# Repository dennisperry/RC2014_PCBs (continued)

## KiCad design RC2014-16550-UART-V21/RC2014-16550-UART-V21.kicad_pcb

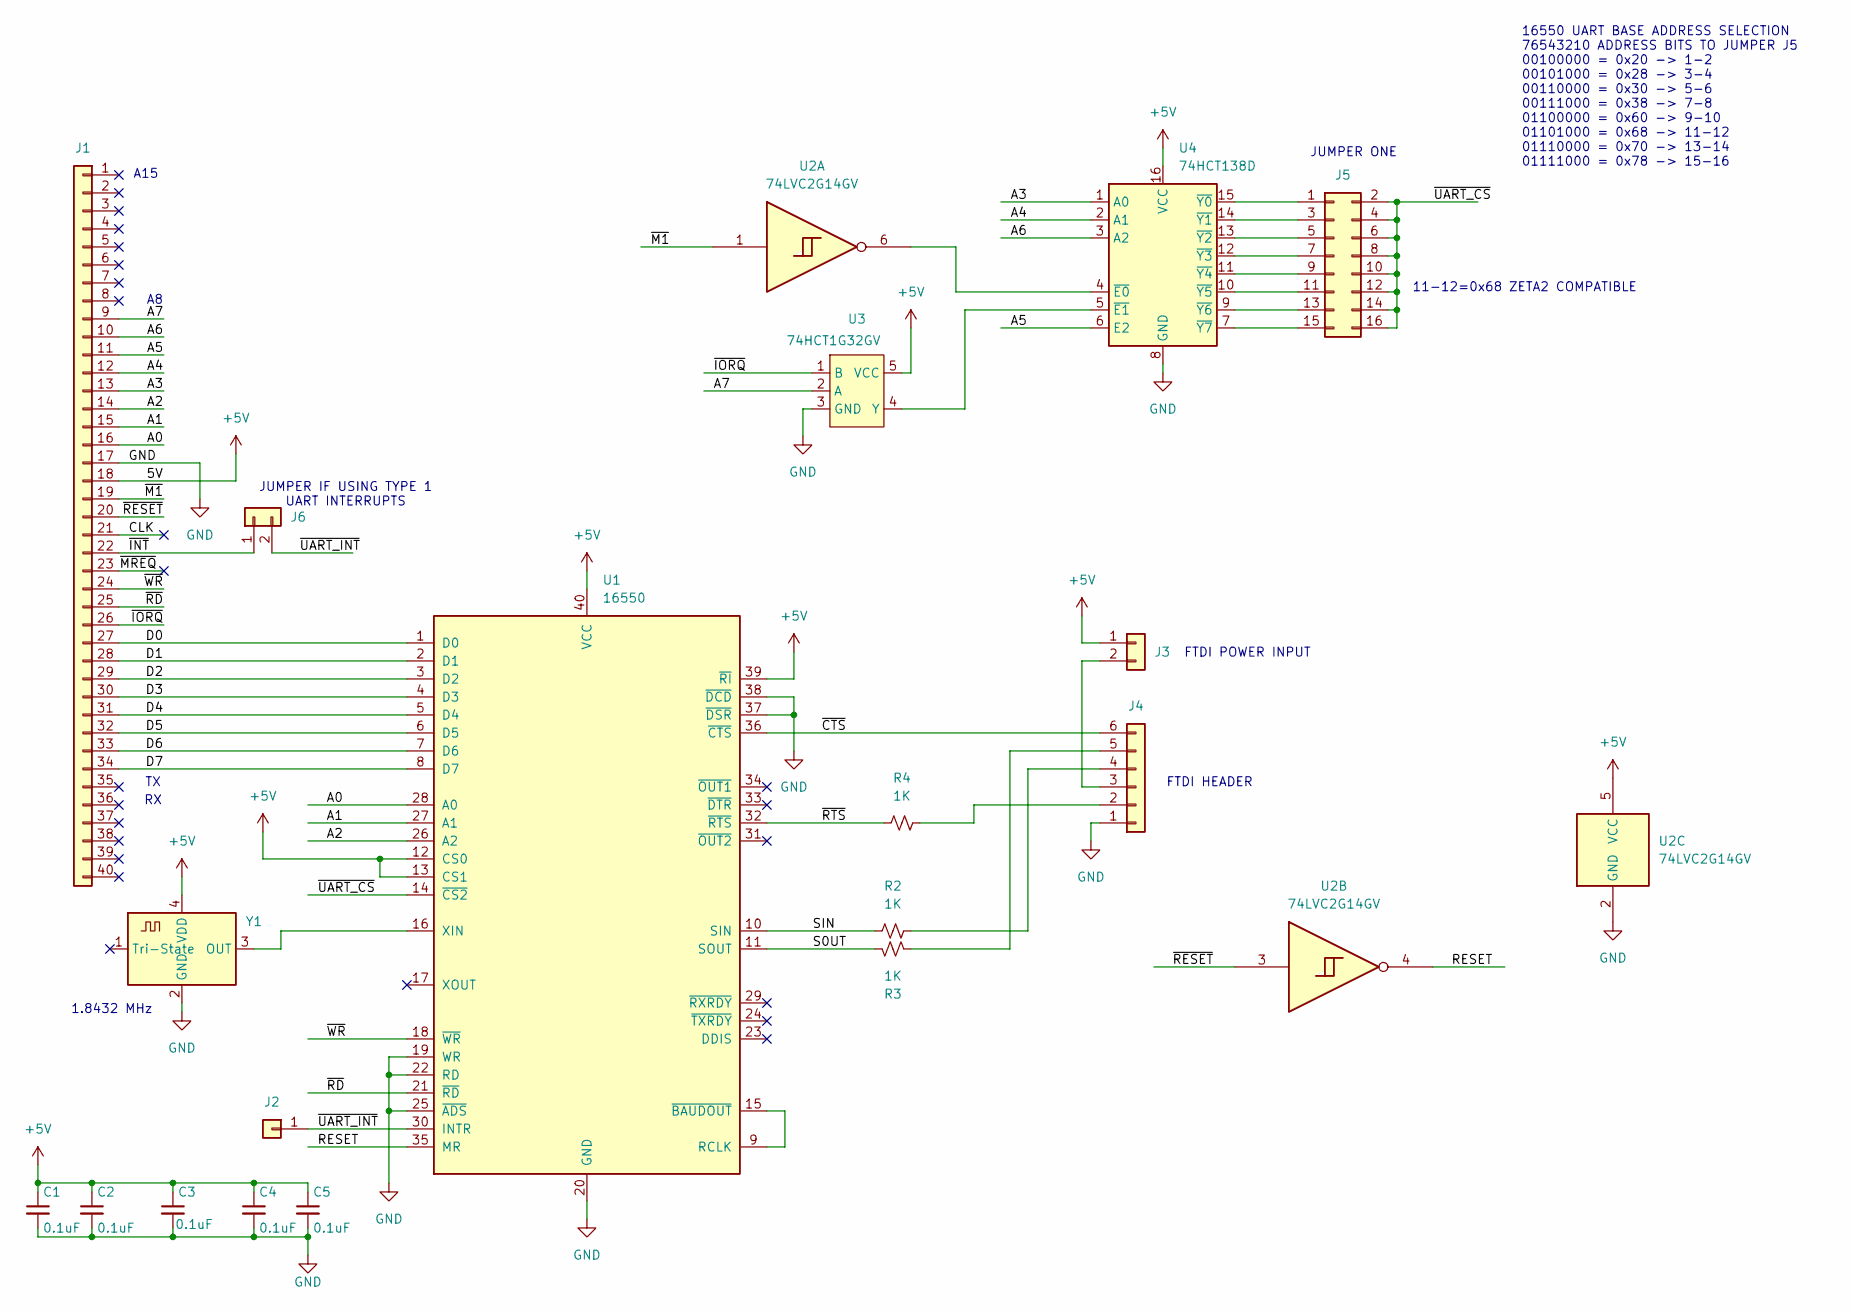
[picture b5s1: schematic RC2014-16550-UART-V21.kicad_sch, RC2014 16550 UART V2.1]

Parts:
C1, C2, C3, C4, C5: 0.1uF; C_0805_2012Metric_Pad1.18x1.45mm_HandSolder
J1: Conn_01x40; PinHeader_1x40_P2.54mm_Vertical
J2: Conn_01x01; PinHeader_1x01_P2.54mm_Vertical
J3, J6: Conn_01x02; PinHeader_1x02_P2.54mm_Vertical
J4: Conn_01x06; PinHeader_1x06_P2.54mm_Vertical
J5: Conn_02x08_Odd_Even; PinHeader_2x08_P2.54mm_Vertical
R2, R3, R4: 1K; R_0805_2012Metric_Pad1.20x1.40mm_HandSolder
U1: 16550; DIP-40_W15.24mm
U2: 74LVC2G14GV; SC-74-6_1.55x2.9mm_P0.95mm
U3: 74HCT1G32GV; SOT-23-5_HandSoldering
U4: 74HCT138D; SOIC-16_4.55x10.3mm_P1.27mm
Y1: ASCO; Oscillator_SMD_EuroQuartz_XO91-4Pin_7.0x5.0mm_HandSoldering

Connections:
+5V: C1.1, C2.1, C3.1, C4.1, C5.1, J1.18, J3.1, U1.12 (CS0), U1.13 (CS1), U1.39 (~RI), U1.40 (VCC), U2.5 (VCC), U3.5 (VCC), U4.16 (VCC), Y1.4 (VDD)
/A0: J1.16, U1.28 (A0)
/A1: J1.15, U1.27 (A1)
/A2: J1.14, U1.26 (A2)
/A3: J1.13, U4.1 (A0)
/A4: J1.12, U4.2 (A1)
/A5: J1.11, U4.6 (E2)
/A6: J1.10, U4.3 (A2)
/A7: J1.9, U3.2 (A)
/CLK: J1.21
/D0: J1.27, U1.1 (D0)
/D1: J1.28, U1.2 (D1)
/D2: J1.29, U1.3 (D2)
/D3: J1.30, U1.4 (D3)
/D4: J1.31, U1.5 (D4)
/D5: J1.32, U1.6 (D5)
/D6: J1.33, U1.7 (D6)
/D7: J1.34, U1.8 (D7)
/RESET: U1.35 (MR), U2.4
/S0UT: R3.2, U1.11 (SOUT)
/SIN: R2.1, U1.10 (SIN)
/~CTS: J4.6, U1.36 (~CTS)
/~INT: J1.22, J6.1
/~IORQ: J1.26, U3.1 (B)
/~M1: J1.19, U2.1
/~MREQ: J1.23
/~RD: J1.25, U1.21 (~RD)
/~RESET: J1.20, U2.3
/~RTS: R4.1, U1.32 (~RTS)
/~UART_CS: J5.2, J5.4, J5.6, J5.8, J5.10, J5.12, J5.14, J5.16, U1.14 (~CS2)
/~UART_INT: J2.1, J6.2, U1.30 (INTR)
/~WR: J1.24, U1.18 (~WR)
GND: C1.2, C2.2, C3.2, C4.2, C5.2, J1.17, J4.1, U1.19 (WR), U1.20 (GND), U1.22 (RD), U1.25 (~ADS), U1.37 (~DSR), U1.38 (~DCD), U2.2 (GND), U3.3 (GND), U4.8 (GND), Y1.2 (GND)
unnamed: J3.2, J4.3
unnamed: J4.2, R4.2
unnamed: J4.4, R2.2
unnamed: J4.5, R3.1
unnamed: J5.1, U4.15 (~Y0)
unnamed: J5.3, U4.14 (~Y1)
unnamed: J5.5, U4.13 (~Y2)
unnamed: J5.7, U4.12 (~Y3)
unnamed: J5.9, U4.11 (~Y4)
unnamed: J5.11, U4.10 (~Y5)
unnamed: J5.13, U4.9 (~Y6)
unnamed: J5.15, U4.7 (~Y7)
unnamed: U1.9 (RCLK), U1.15 (~BAUDOUT)
unnamed: U1.16 (XIN), Y1.3 (OUT)
unnamed: U3.4 (Y), U4.5 (~E1)
unnamed: U2.6, U4.4 (~E0)

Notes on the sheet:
16550 UART BASE ADDRESS SELECTION 76543210 ADDRESS BITS TO JUMPER J5 00100000 = 0x20 -> 1-2 00101000 = 0x28 -> 3-4 00110000 = 0x30 -> 5-6 00111000 = 0x38 -> 7-8 01100000 = 0x60 -> 9-10 01101000 = 0x68 -> 11-12 01110000 = 0x70 -> 13-14 01111000 = 0x78 -> 15-16
11-12=0x68 ZETA2 COMPATIBLE
JUMPER ONE
1.8432 MHz
JUMPER IF USING TYPE 1 UART INTERRUPTS
FTDI POWER INPUT
A15
FTDI HEADER

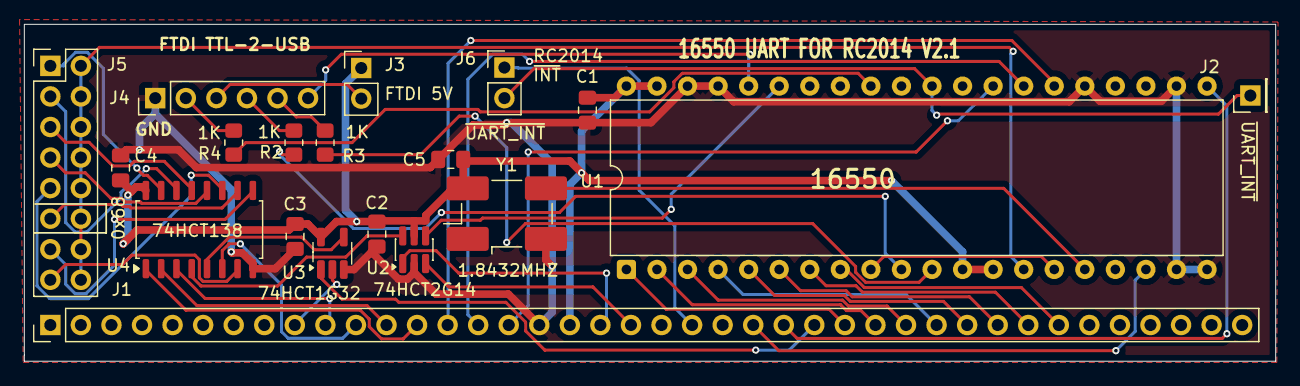
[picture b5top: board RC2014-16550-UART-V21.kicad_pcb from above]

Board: 2 copper layers, 104.0 x 28.0 mm, 19 parts (0 on the bottom side), 47 nets.

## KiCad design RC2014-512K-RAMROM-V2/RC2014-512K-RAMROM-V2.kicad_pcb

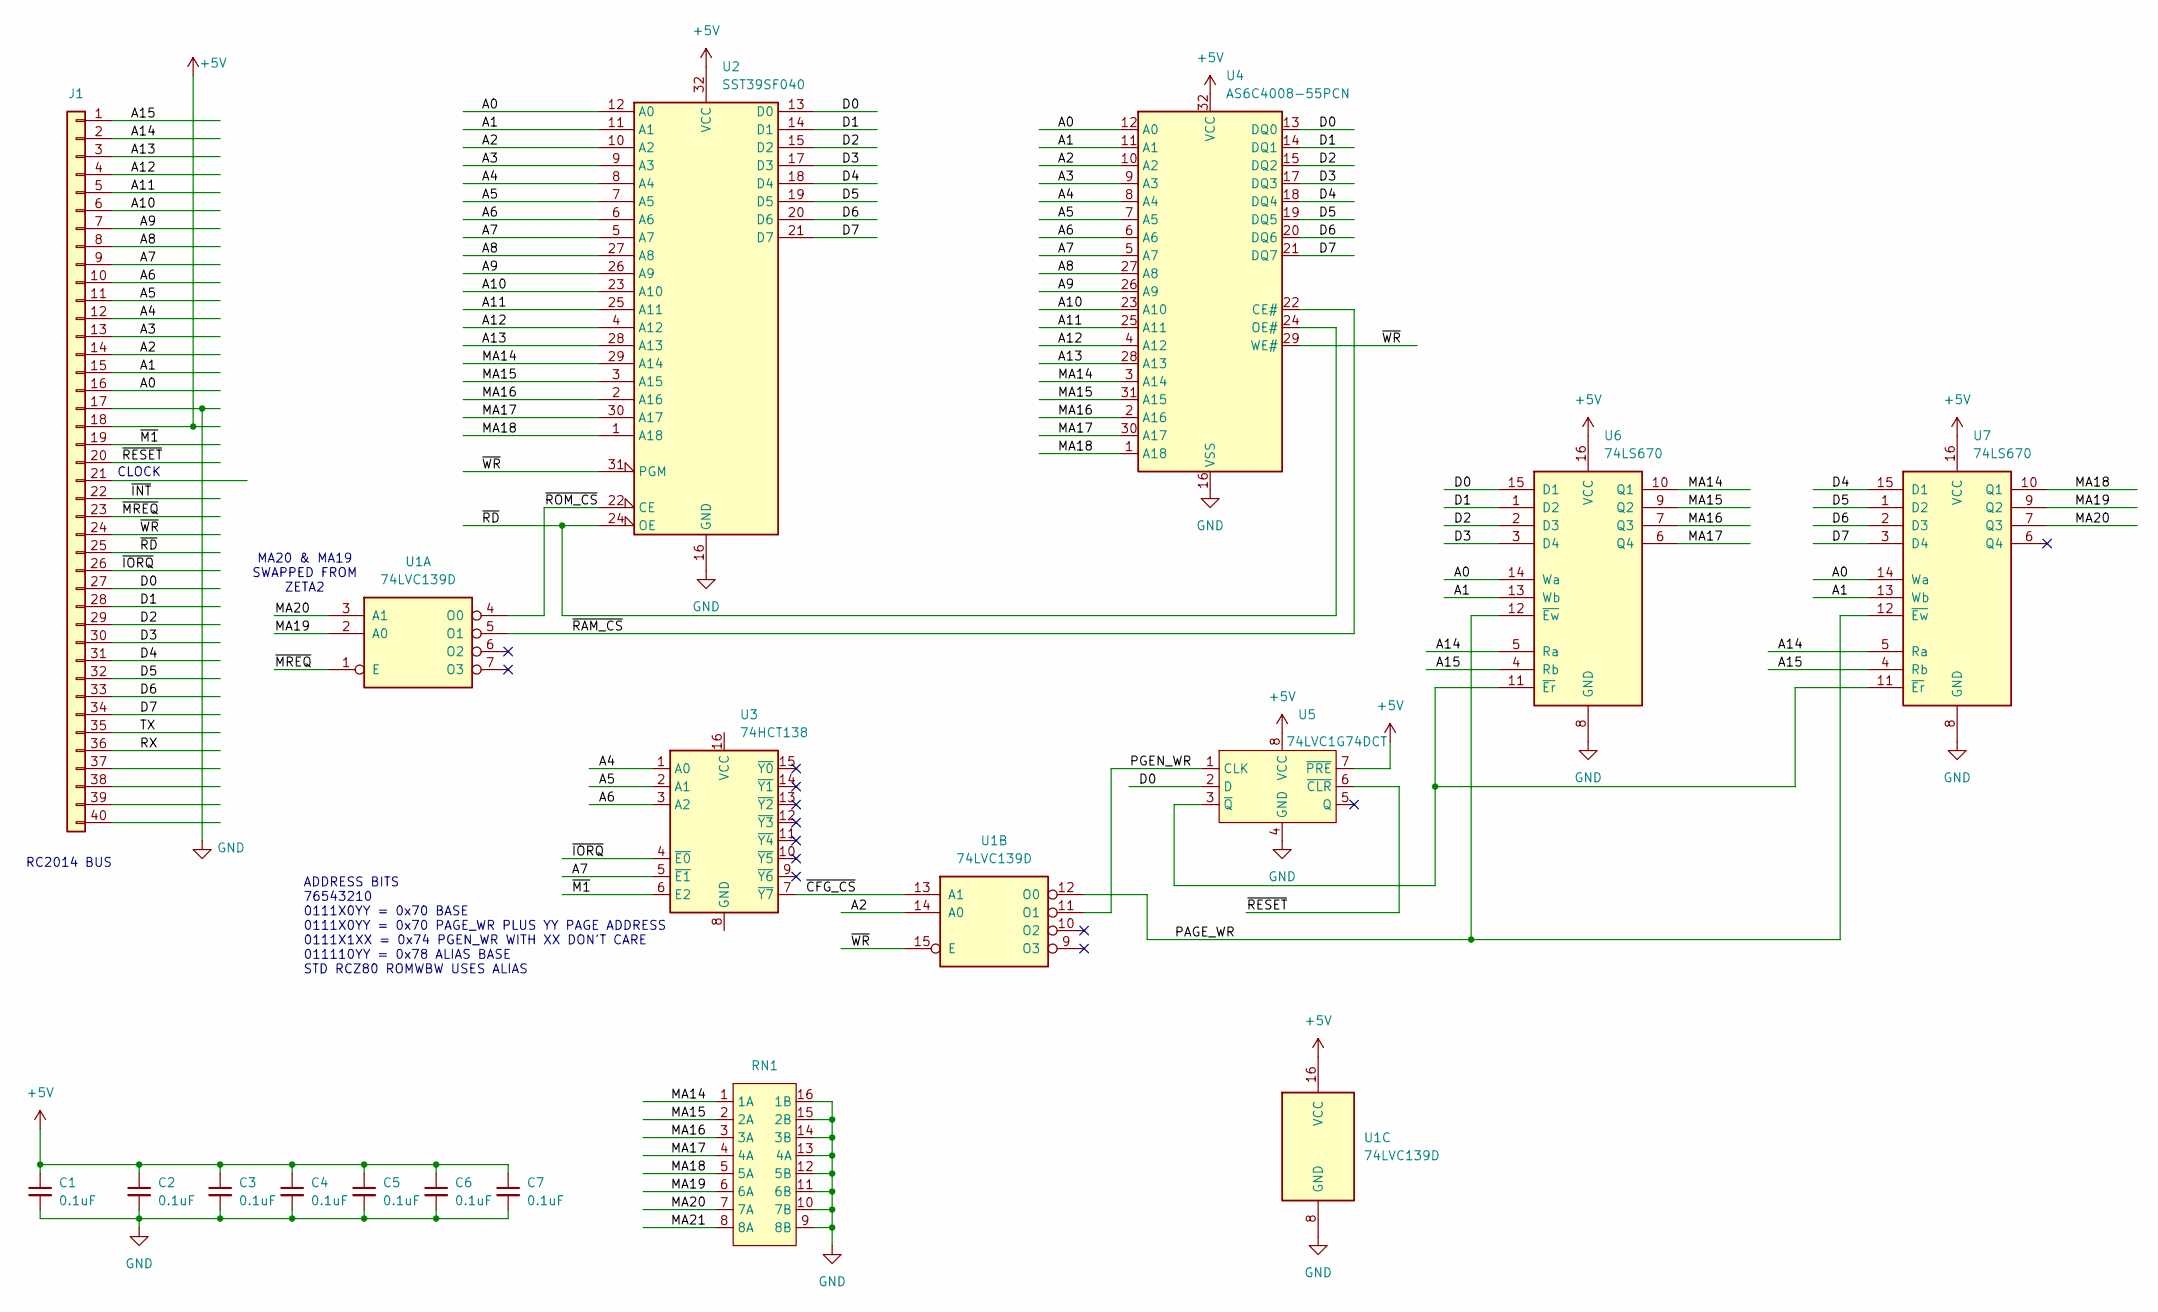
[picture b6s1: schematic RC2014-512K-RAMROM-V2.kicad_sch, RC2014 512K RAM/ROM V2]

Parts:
C1, C2, C3, C4, C5, C6, C7: 0.1uF; C_0805_2012Metric_Pad1.18x1.45mm_HandSolder
J1: Conn_01x40; PinHeader_1x40_P2.54mm_Vertical
RN1: SOIC-16W_5.3x10.2mm_P1.27mm
U1: 74LVC139D; SOIC-16_4.55x10.3mm_P1.27mm
U2: SST39SF040; DIP_Socket-32_DP_W11.9mm_W12.7mm_W15.24mm_W17.78mm_W18.5mm_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
U3: 74HCT138; SOIC-16_4.55x10.3mm_P1.27mm
U4: AS6C4008-55PCN; SOP-32_11.305x20.495mm_P1.27mm
U5: 74LVC1G74DCT; SSOP-8_2.95x2.8mm_P0.65mm
U6, U7: 74LS670; SOIC-16_4.55x10.3mm_P1.27mm

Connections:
+5V: C1.1, C2.1, C3.1, C4.1, C5.1, C6.1, C7.1, J1.18, U1.16 (VCC), U2.32 (VCC), U4.32 (VCC), U5.7 (~PRE), U5.8 (VCC), U6.16 (VCC), U7.16 (VCC)
/A0: J1.16, U2.12 (A0), U4.12 (A0), U6.14 (Wa), U7.14 (Wa)
/A1: J1.15, U2.11 (A1), U4.11 (A1), U6.13 (Wb), U7.13 (Wb)
/A2: J1.14, U1.14 (A0), U2.10 (A2), U4.10 (A2)
/A3: J1.13, U2.9 (A3), U4.9 (A3)
/A4: J1.12, U2.8 (A4), U3.1 (A0), U4.8 (A4)
/A5: J1.11, U2.7 (A5), U3.2 (A1), U4.7 (A5)
/A6: J1.10, U2.6 (A6), U3.3 (A2), U4.6 (A6)
/A7: J1.9, U2.5 (A7), U3.5 (~E1), U4.5 (A7)
/A8: J1.8, U2.27 (A8), U4.27 (A8)
/A9: J1.7, U2.26 (A9), U4.26 (A9)
/A10: J1.6, U2.23 (A10), U4.23 (A10)
/A11: J1.5, U2.25 (A11), U4.25 (A11)
/A12: J1.4, U2.4 (A12), U4.4 (A12)
/A13: J1.3, U2.28 (A13), U4.28 (A13)
/A14: J1.2, U6.5 (Ra), U7.5 (Ra)
/A15: J1.1, U6.4 (Rb), U7.4 (Rb)
/D0: J1.27, U2.13 (D0), U4.13 (DQ0), U5.2 (D), U6.15 (D1)
/D1: J1.28, U2.14 (D1), U4.14 (DQ1), U6.1 (D2)
/D2: J1.29, U2.15 (D2), U4.15 (DQ2), U6.2 (D3)
/D3: J1.30, U2.17 (D3), U4.17 (DQ3), U6.3 (D4)
/D4: J1.31, U2.18 (D4), U4.18 (DQ4), U7.15 (D1)
/D5: J1.32, U2.19 (D5), U4.19 (DQ5), U7.1 (D2)
/D6: J1.33, U2.20 (D6), U4.20 (DQ6), U7.2 (D3)
/D7: J1.34, U2.21 (D7), U4.21 (DQ7), U7.3 (D4)
/MA14: RN1.1 (1A), U2.29 (A14), U4.3 (A14), U6.10 (Q1)
/MA15: RN1.2 (2A), U2.3 (A15), U4.31 (A15), U6.9 (Q2)
/MA16: RN1.3 (3A), U2.2 (A16), U4.2 (A16), U6.7 (Q3)
/MA17: RN1.4 (4A), U2.30 (A17), U4.30 (A17), U6.6 (Q4)
/MA18: RN1.5 (5A), U2.1 (A18), U4.1 (A18), U7.10 (Q1)
/MA19: RN1.6 (6A), U1.2 (A0), U7.9 (Q2)
/MA20: RN1.7 (7A), U1.3 (A1), U7.7 (Q3)
/MA21: RN1.8 (8A)
/PAGE_WR: U1.12 (O0), U6.12 (~Ew), U7.12 (~Ew)
/PGEN_WR: U1.11 (O1), U5.1 (CLK)
/RX: J1.36
/TX: J1.35
/~CFG_CS: U1.13 (A1), U3.7 (~Y7)
/~INT: J1.22
/~IORQ: J1.26, U3.4 (~E0)
/~M1: J1.19, U3.6 (E2)
/~MREQ: J1.23, U1.1 (E)
/~RAM_CS: U1.5 (O1), U4.22 (CE#)
/~RD: J1.25, U2.24 (OE), U4.24 (OE#)
/~RESET: J1.20, U5.6 (~CLR)
/~ROM_CS: U1.4 (O0), U2.22 (CE)
/~WR: J1.24, U1.15 (E), U2.31 (PGM), U4.29 (WE#)
GND: C1.2, C2.2, C3.2, C4.2, C5.2, C6.2, C7.2, J1.17, RN1.9 (8B), RN1.10 (7B), RN1.11 (6B), RN1.12 (5B), RN1.13 (4A), RN1.14 (3B), RN1.15 (2B), RN1.16 (1B), U1.8 (GND), U2.16 (GND), U4.16 (VSS), U5.4 (GND), U6.8 (GND), U7.8 (GND)
unnamed: U5.3 (~Q), U6.11 (~Er), U7.11 (~Er)

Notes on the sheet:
ADDRESS BITS 76543210 0111X0YY = 0x70 BASE 0111X0YY = 0x70 PAGE_WR PLUS YY PAGE ADDRESS 0111X1XX = 0x74 PGEN_WR WITH XX DON'T CARE 011110YY = 0x78 ALIAS BASE STD RCZ80 ROMWBW USES ALIAS
RC2014 BUS
MA20 & MA19 SWAPPED FROM ZETA2
CLOCK

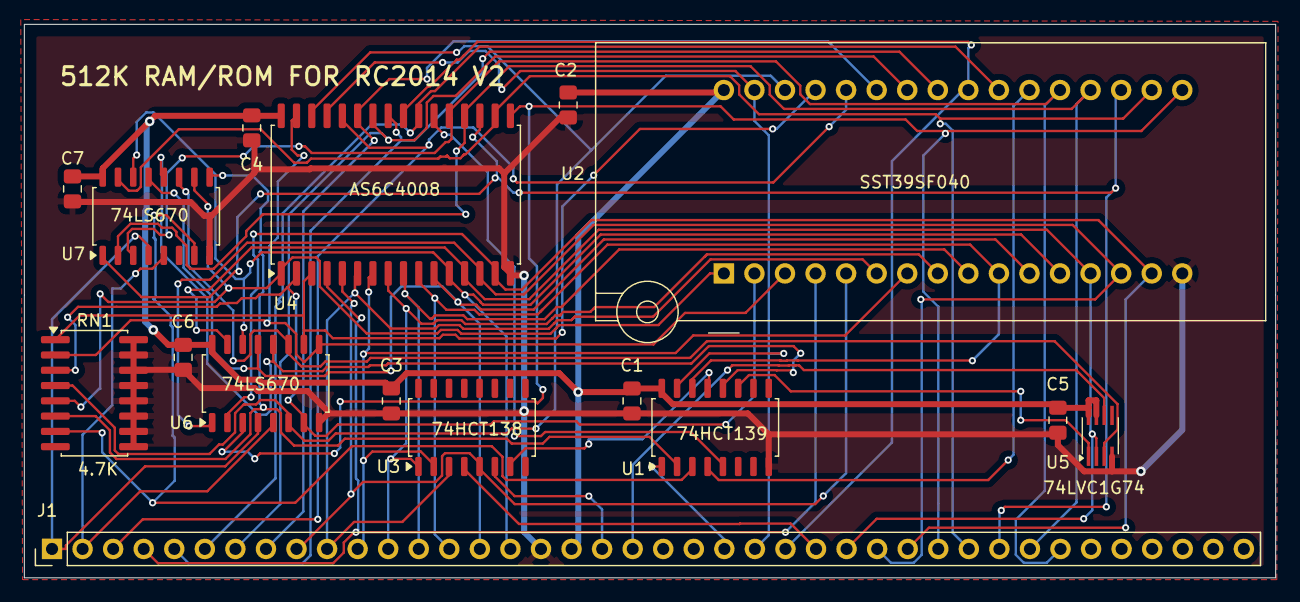
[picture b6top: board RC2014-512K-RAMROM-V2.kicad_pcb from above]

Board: 2 copper layers, 104.0 x 46.0 mm, 16 parts (0 on the bottom side), 45 nets.

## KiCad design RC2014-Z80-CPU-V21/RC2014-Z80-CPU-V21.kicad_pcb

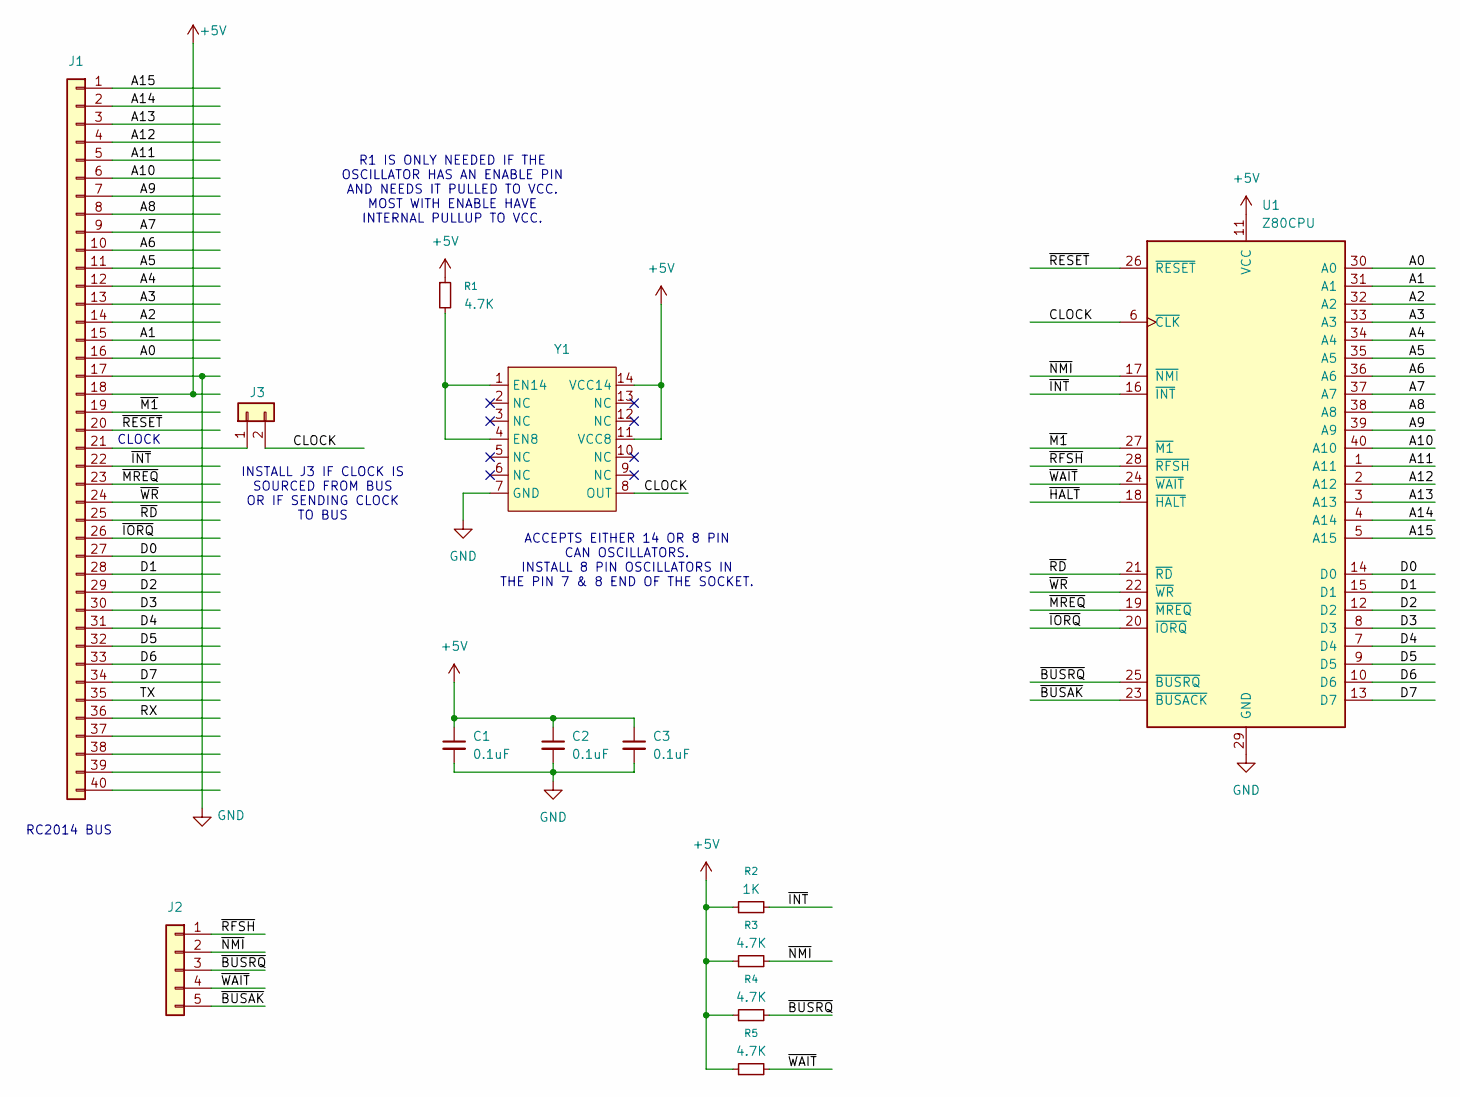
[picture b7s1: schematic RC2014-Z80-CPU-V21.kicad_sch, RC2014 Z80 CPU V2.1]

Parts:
C1, C2, C3: 0.1uF; C_0805_2012Metric_Pad1.18x1.45mm_HandSolder
J1: Conn_01x40; PinHeader_1x40_P2.54mm_Vertical
J2: Conn_01x05; PinHeader_1x05_P2.54mm_Vertical
J3: Conn_01x02; PinHeader_2x01_P2.54mm_Vertical
R1, R3, R4, R5: 4.7K; R_0805_2012Metric_Pad1.20x1.40mm_HandSolder
R2: 1K; R_0805_2012Metric_Pad1.20x1.40mm_HandSolder
U1: Z80CPU; DIP-40_W15.24mm
Y1: DIP-14_W7.62mm

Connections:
+5V: C1.1, C2.1, C3.1, J1.18, R1.1, R2.1, R3.1, R4.1, R5.1, U1.11 (VCC), Y1.11 (VCC8), Y1.14 (VCC14)
/A0: J1.16, U1.30 (A0)
/A1: J1.15, U1.31 (A1)
/A2: J1.14, U1.32 (A2)
/A3: J1.13, U1.33 (A3)
/A4: J1.12, U1.34 (A4)
/A5: J1.11, U1.35 (A5)
/A6: J1.10, U1.36 (A6)
/A7: J1.9, U1.37 (A7)
/A8: J1.8, U1.38 (A8)
/A9: J1.7, U1.39 (A9)
/A10: J1.6, U1.40 (A10)
/A11: J1.5, U1.1 (A11)
/A12: J1.4, U1.2 (A12)
/A13: J1.3, U1.3 (A13)
/A14: J1.2, U1.4 (A14)
/A15: J1.1, U1.5 (A15)
/CLOCK: J3.2, U1.6 (~CLK), Y1.8 (OUT)
/D0: J1.27, U1.14 (D0)
/D1: J1.28, U1.15 (D1)
/D2: J1.29, U1.12 (D2)
/D3: J1.30, U1.8 (D3)
/D4: J1.31, U1.7 (D4)
/D5: J1.32, U1.9 (D5)
/D6: J1.33, U1.10 (D6)
/D7: J1.34, U1.13 (D7)
/RX: J1.36
/TX: J1.35
/~BUSAK: J2.5, U1.23 (~BUSACK)
/~BUSRQ: J2.3, R4.2, U1.25 (~BUSRQ)
/~HALT: U1.18 (~HALT)
/~INT: J1.22, R2.2, U1.16 (~INT)
/~IORQ: J1.26, U1.20 (~IORQ)
/~M1: J1.19, U1.27 (~M1)
/~MREQ: J1.23, U1.19 (~MREQ)
/~NMI: J2.2, R3.2, U1.17 (~NMI)
/~RD: J1.25, U1.21 (~RD)
/~RESET: J1.20, U1.26 (~RESET)
/~RFSH: J2.1, U1.28 (~RFSH)
/~WAIT: J2.4, R5.2, U1.24 (~WAIT)
/~WR: J1.24, U1.22 (~WR)
GND: C1.2, C2.2, C3.2, J1.17, U1.29 (GND), Y1.7 (GND)
unnamed: J1.21, J3.1
unnamed: R1.2, Y1.1 (EN14), Y1.4 (EN8)

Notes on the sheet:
RC2014 BUS
INSTALL J3 IF CLOCK IS SOURCED FROM BUS OR IF SENDING CLOCK TO BUS
ACCEPTS EITHER 14 OR 8 PIN CAN OSCILLATORS. INSTALL 8 PIN OSCILLATORS IN THE PIN 7 & 8 END OF THE SOCKET.
CLOCK
R1 IS ONLY NEEDED IF THE OSCILLATOR HAS AN ENABLE PIN AND NEEDS IT PULLED TO VCC. MOST WITH ENABLE HAVE INTERNAL PULLUP TO VCC.

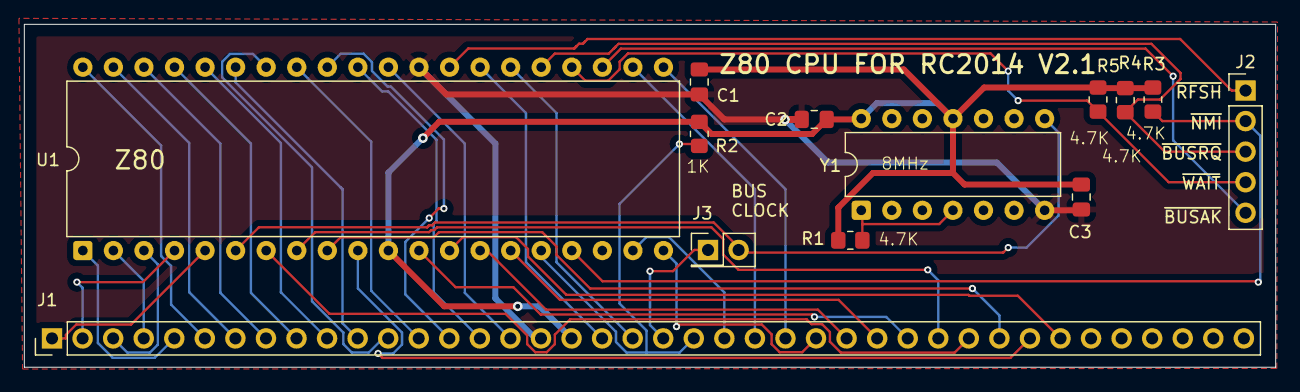
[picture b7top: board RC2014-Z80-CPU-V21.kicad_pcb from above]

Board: 2 copper layers, 104.0 x 28.5 mm, 13 parts (0 on the bottom side), 41 nets.

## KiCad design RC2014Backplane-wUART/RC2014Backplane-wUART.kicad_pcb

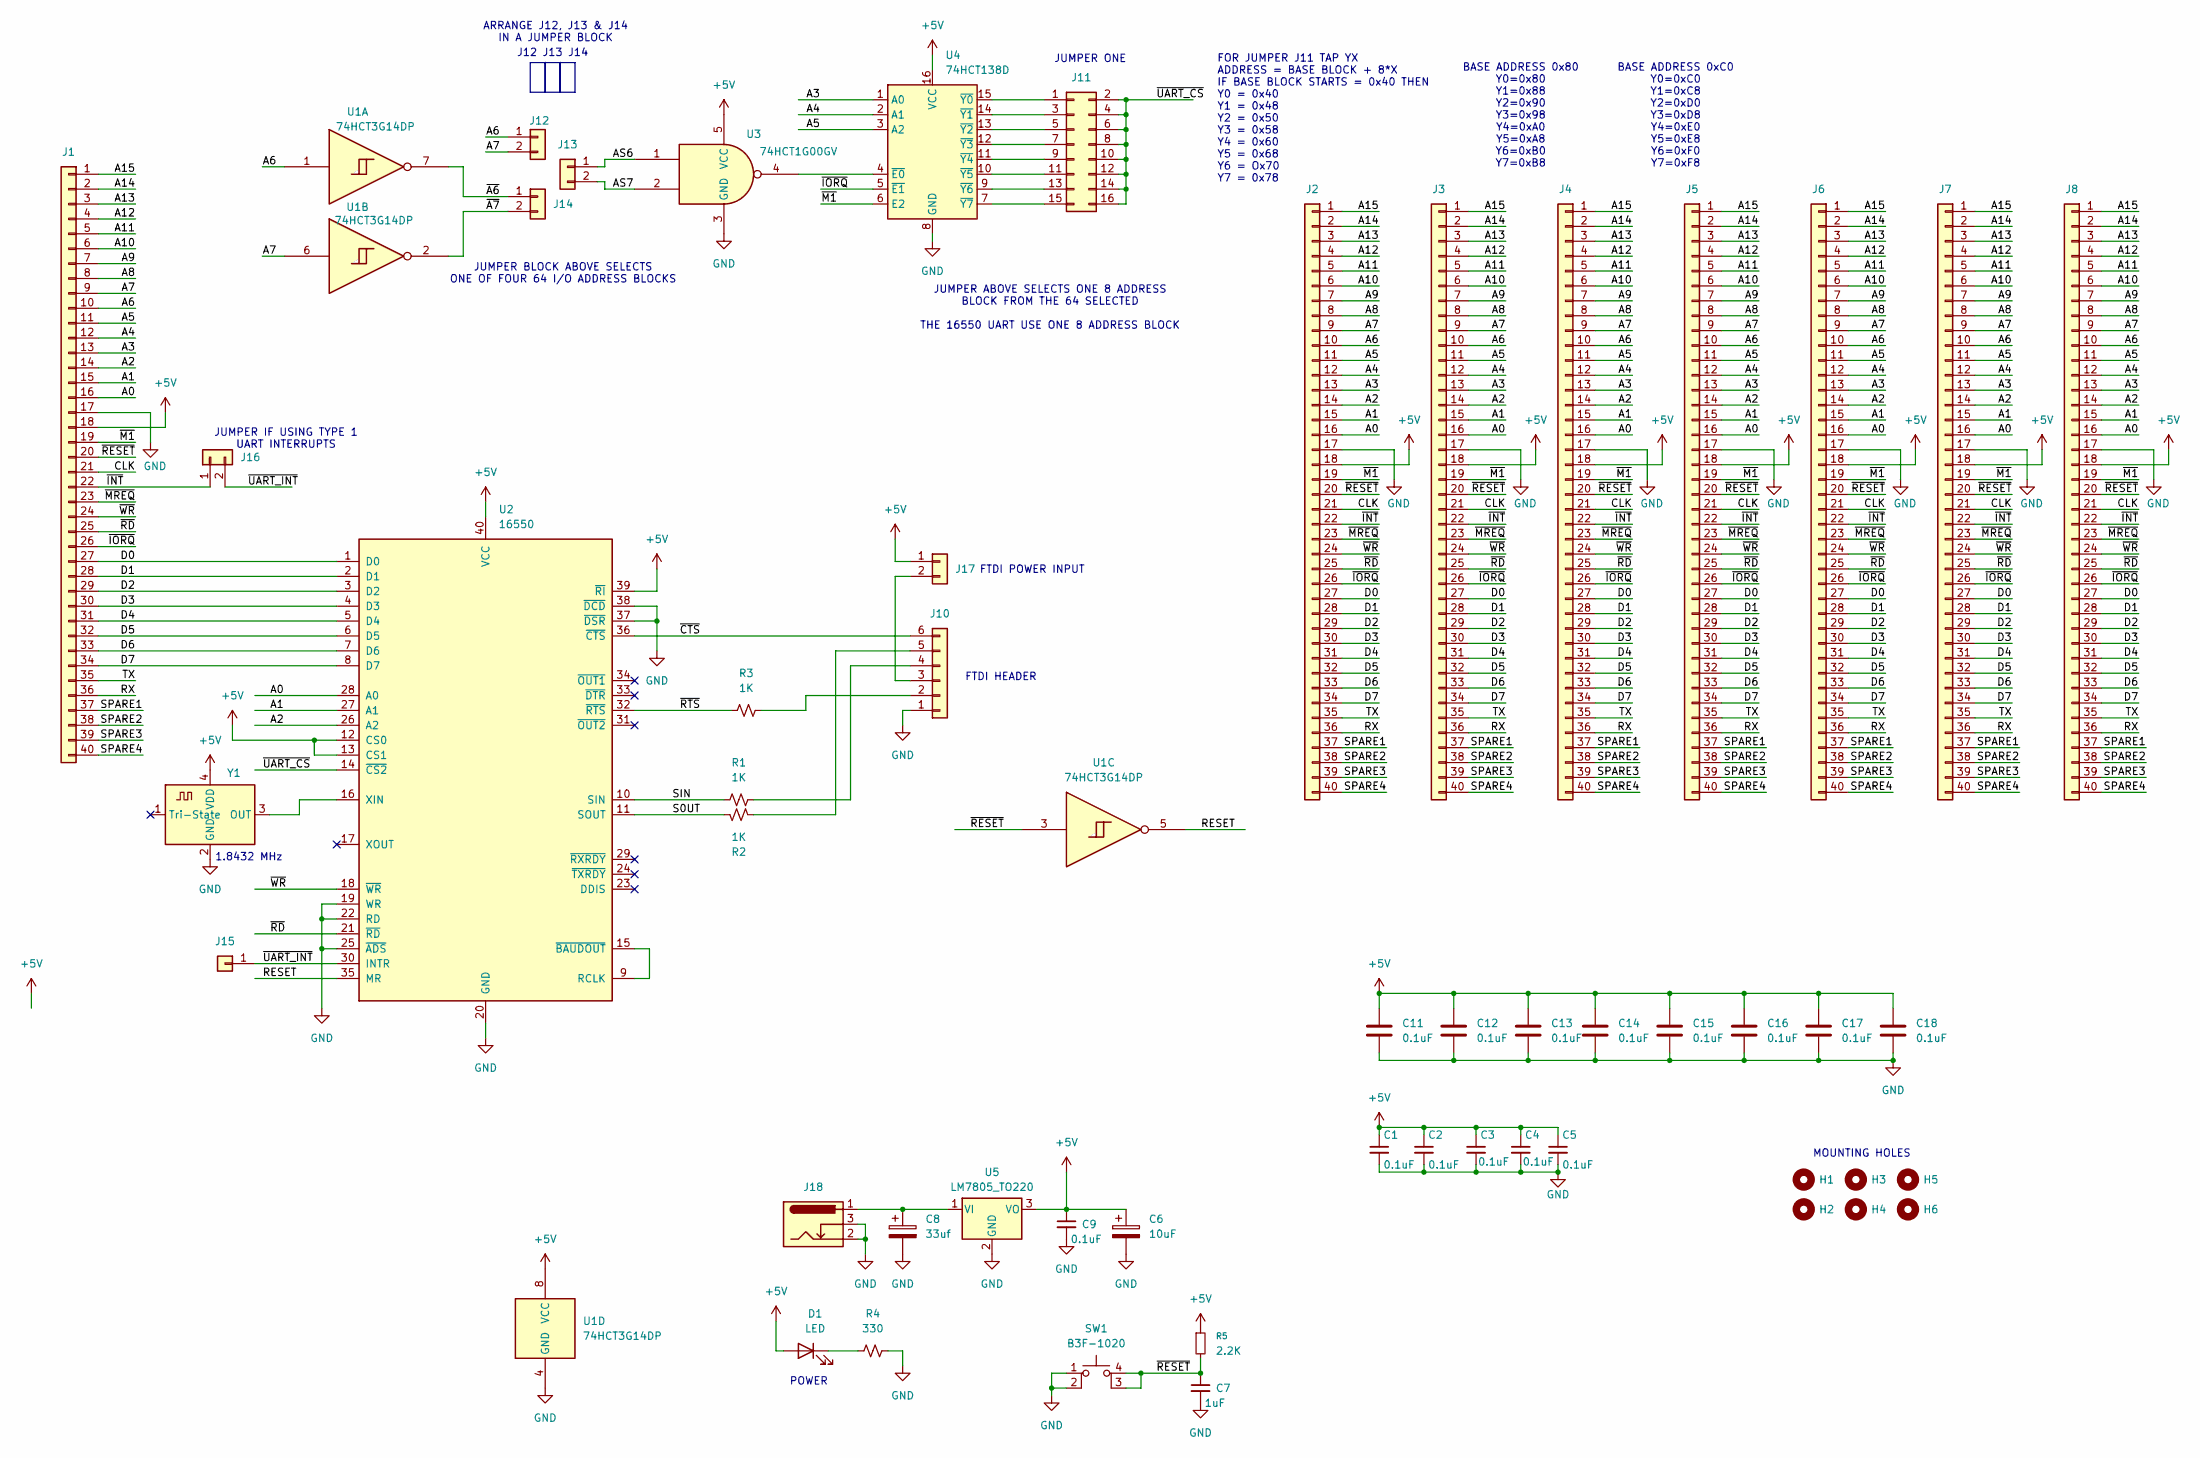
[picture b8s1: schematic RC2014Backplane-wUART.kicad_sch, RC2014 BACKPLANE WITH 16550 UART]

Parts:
C1, C2, C3, C4, C5, C9: 0.1uF; C_0805_2012Metric_Pad1.18x1.45mm_HandSolder
C6: 10uF; CP_Radial_D4.0mm_P2.00mm
C7: 1uF; C_0805_2012Metric_Pad1.18x1.45mm_HandSolder
C8: 33uf; CP_Radial_D4.0mm_P2.00mm
C11, C12, C13, C14, C15, C16, C17, C18: 0.1uF; C_Disc_D3.4mm_W2.1mm_P2.50mm
D1: LED; LED_D3.0mm
H1, H2, H3, H4, H5, H6: MountingHole; MountingHole_4.5mm
J1, J2, J3, J4, J5, J6, J7, J8: Conn_01x40; PinHeader_1x40_P2.54mm_Vertical
J10: Conn_01x06; PinHeader_1x06_P2.54mm_Vertical
J11: Conn_02x08_Odd_Even; PinHeader_2x08_P2.54mm_Vertical
J12, J13, J14, J16, J17: Conn_01x02; PinHeader_1x02_P2.54mm_Vertical
J15: Conn_01x01; PinHeader_1x01_P2.54mm_Vertical
J18: Barrel_Jack_Switch; BarrelJack_Horizontal
R1, R2, R3: 1K; R_0805_2012Metric_Pad1.20x1.40mm_HandSolder
R4: 330; R_0805_2012Metric_Pad1.20x1.40mm_HandSolder
R5: 2.2K; R_0805_2012Metric_Pad1.20x1.40mm_HandSolder
SW1: B3F-1020; SW_TH_Tactile_Omron_B3F-102x
U1: 74HCT3G14DP; TSSOP-8_3x3mm_P0.65mm
U2: 16550; DIP-40_W15.24mm
U3: 74HCT1G00GV; SC-74A-5_1.55x2.9mm_P0.95mm
U4: 74HCT138D; SOIC-16_4.55x10.3mm_P1.27mm
U5: LM7805_TO220; TO-220-3_Horizontal_TabDown
Y1: ASCO; Oscillator_SMD_EuroQuartz_XO91-4Pin_7.0x5.0mm_HandSoldering

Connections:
+5V: C1.1, C2.1, C3.1, C4.1, C5.1, C6.1, C9.1, C11.1, C12.1, C13.1, C14.1, C15.1, C16.1, C17.1, C18.1, D1.2 (A), J1.18, J2.18, J3.18, J4.18, J5.18, J6.18, J7.18, J8.18, J17.1, R5.1, U1.8 (VCC), U2.12 (CS0), U2.13 (CS1), U2.39 (~RI), U2.40 (VCC), U3.5 (VCC), U4.16 (VCC), U5.3 (VO), Y1.4 (VDD)
/A0: J1.16, J2.16, J3.16, J4.16, J5.16, J6.16, J7.16, J8.16, U2.28 (A0)
/A1: J1.15, J2.15, J3.15, J4.15, J5.15, J6.15, J7.15, J8.15, U2.27 (A1)
/A2: J1.14, J2.14, J3.14, J4.14, J5.14, J6.14, J7.14, J8.14, U2.26 (A2)
/A3: J1.13, J2.13, J3.13, J4.13, J5.13, J6.13, J7.13, J8.13, U4.1 (A0)
/A4: J1.12, J2.12, J3.12, J4.12, J5.12, J6.12, J7.12, J8.12, U4.2 (A1)
/A5: J1.11, J2.11, J3.11, J4.11, J5.11, J6.11, J7.11, J8.11, U4.3 (A2)
/A6: J1.10, J2.10, J3.10, J4.10, J5.10, J6.10, J7.10, J8.10, J12.1, U1.1
/A7: J1.9, J2.9, J3.9, J4.9, J5.9, J6.9, J7.9, J8.9, J12.2, U1.6
/A8: J1.8, J2.8, J3.8, J4.8, J5.8, J6.8, J7.8, J8.8
/A9: J1.7, J2.7, J3.7, J4.7, J5.7, J6.7, J7.7, J8.7
/A10: J1.6, J2.6, J3.6, J4.6, J5.6, J6.6, J7.6, J8.6
/A11: J1.5, J2.5, J3.5, J4.5, J5.5, J6.5, J7.5, J8.5
/A12: J1.4, J2.4, J3.4, J4.4, J5.4, J6.4, J7.4, J8.4
/A13: J1.3, J2.3, J3.3, J4.3, J5.3, J6.3, J7.3, J8.3
/A14: J1.2, J2.2, J3.2, J4.2, J5.2, J6.2, J7.2, J8.2
/A15: J1.1, J2.1, J3.1, J4.1, J5.1, J6.1, J7.1, J8.1
/AS6: J13.1, U3.1
/AS7: J13.2, U3.2
/CLK: J1.21, J2.21, J3.21, J4.21, J5.21, J6.21, J7.21, J8.21
/D0: J1.27, J2.27, J3.27, J4.27, J5.27, J6.27, J7.27, J8.27, U2.1 (D0)
/D1: J1.28, J2.28, J3.28, J4.28, J5.28, J6.28, J7.28, J8.28, U2.2 (D1)
/D2: J1.29, J2.29, J3.29, J4.29, J5.29, J6.29, J7.29, J8.29, U2.3 (D2)
/D3: J1.30, J2.30, J3.30, J4.30, J5.30, J6.30, J7.30, J8.30, U2.4 (D3)
/D4: J1.31, J2.31, J3.31, J4.31, J5.31, J6.31, J7.31, J8.31, U2.5 (D4)
/D5: J1.32, J2.32, J3.32, J4.32, J5.32, J6.32, J7.32, J8.32, U2.6 (D5)
/D6: J1.33, J2.33, J3.33, J4.33, J5.33, J6.33, J7.33, J8.33, U2.7 (D6)
/D7: J1.34, J2.34, J3.34, J4.34, J5.34, J6.34, J7.34, J8.34, U2.8 (D7)
/RESET: U1.5, U2.35 (MR)
/RX: J1.36, J2.36, J3.36, J4.36, J5.36, J6.36, J7.36, J8.36
/S0UT: R2.2, U2.11 (SOUT)
/SIN: R1.1, U2.10 (SIN)
/SPARE1: J1.37, J2.37, J3.37, J4.37, J5.37, J6.37, J7.37, J8.37
/SPARE2: J1.38, J2.38, J3.38, J4.38, J5.38, J6.38, J7.38, J8.38
/SPARE3: J1.39, J2.39, J3.39, J4.39, J5.39, J6.39, J7.39, J8.39
/SPARE4: J1.40, J2.40, J3.40, J4.40, J5.40, J6.40, J7.40, J8.40
/TX: J1.35, J2.35, J3.35, J4.35, J5.35, J6.35, J7.35, J8.35
/~A6: J14.1, U1.7
/~A7: J14.2, U1.2
/~CTS: J10.6, U2.36 (~CTS)
/~INT: J1.22, J2.22, J3.22, J4.22, J5.22, J6.22, J7.22, J8.22, J16.1
/~IORQ: J1.26, J2.26, J3.26, J4.26, J5.26, J6.26, J7.26, J8.26, U4.5 (~E1)
/~M1: J1.19, J2.19, J3.19, J4.19, J5.19, J6.19, J7.19, J8.19, U4.6 (E2)
/~MREQ: J1.23, J2.23, J3.23, J4.23, J5.23, J6.23, J7.23, J8.23
/~RD: J1.25, J2.25, J3.25, J4.25, J5.25, J6.25, J7.25, J8.25, U2.21 (~RD)
/~RESET: C7.1, J1.20, J2.20, J3.20, J4.20, J5.20, J6.20, J7.20, J8.20, R5.2, SW1.3 (K), SW1.4 (A), U1.3
/~RTS: R3.1, U2.32 (~RTS)
/~UART_CS: J11.2, J11.4, J11.6, J11.8, J11.10, J11.12, J11.14, J11.16, U2.14 (~CS2)
/~UART_INT: J15.1, J16.2, U2.30 (INTR)
/~WR: J1.24, J2.24, J3.24, J4.24, J5.24, J6.24, J7.24, J8.24, U2.18 (~WR)
GND: C1.2, C2.2, C3.2, C4.2, C5.2, C6.2, C7.2, C8.2, C9.2, C11.2, C12.2, C13.2, C14.2, C15.2, C16.2, C17.2, C18.2, J1.17, J2.17, J3.17, J4.17, J5.17, J6.17, J7.17, J8.17, J10.1, J18.2, J18.3, R4.2, SW1.1, SW1.2, U1.4 (GND), U2.19 (WR), U2.20 (GND), U2.22 (RD), U2.25 (~ADS), U2.37 (~DSR), U2.38 (~DCD), U3.3 (GND), U4.8 (GND), U5.2 (GND), Y1.2 (GND)
unnamed: D1.1 (K), R4.1
unnamed: J10.2, R3.2
unnamed: J10.3, J17.2
unnamed: J10.4, R1.2
unnamed: J10.5, R2.1
unnamed: J11.1, U4.15 (~Y0)
unnamed: J11.3, U4.14 (~Y1)
unnamed: J11.5, U4.13 (~Y2)
unnamed: J11.7, U4.12 (~Y3)
unnamed: J11.9, U4.11 (~Y4)
unnamed: J11.11, U4.10 (~Y5)
unnamed: J11.13, U4.9 (~Y6)
unnamed: J11.15, U4.7 (~Y7)
unnamed: U2.9 (RCLK), U2.15 (~BAUDOUT)
unnamed: U2.16 (XIN), Y1.3 (OUT)
unnamed: U3.4, U4.4 (~E0)
unnamed: C8.1, J18.1, U5.1 (VI)

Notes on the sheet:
POWER
BASE ADDRESS 0x80 Y0=0x80 Y1=0x88 Y2=0x90 Y3=0x98 Y4=0xA0 Y5=0xA8 Y6=0xB0 Y7=0xB8
JUMPER ABOVE SELECTS ONE 8 ADDRESS BLOCK FROM THE 64 SELECTED THE 16550 UART USE ONE 8 ADDRESS BLOCK
ARRANGE J12, J13 & J14 IN A JUMPER BLOCK
MOUNTING HOLES
JUMPER ONE
JUMPER BLOCK ABOVE SELECTS ONE OF FOUR 64 I/O ADDRESS BLOCKS
FOR JUMPER J11 TAP YX ADDRESS = BASE BLOCK + 8*X IF BASE BLOCK STARTS = 0x40 THEN Y0 = 0x40 Y1 = 0x48 Y2 = 0x50 Y3 = 0x58 Y4 = 0x60 Y5 = 0x68 Y6 = Ox70 Y7 = 0x78
1.8432 MHz
J12 J13 J14
JUMPER IF USING TYPE 1 UART INTERRUPTS
BASE ADDRESS 0xC0 Y0=0xC0 Y1=0xC8 Y2=0xD0 Y3=0xD8 Y4=0xE0 Y5=0xE8 Y6=0xF0 Y7=0xF8
FTDI POWER INPUT
FTDI HEADER

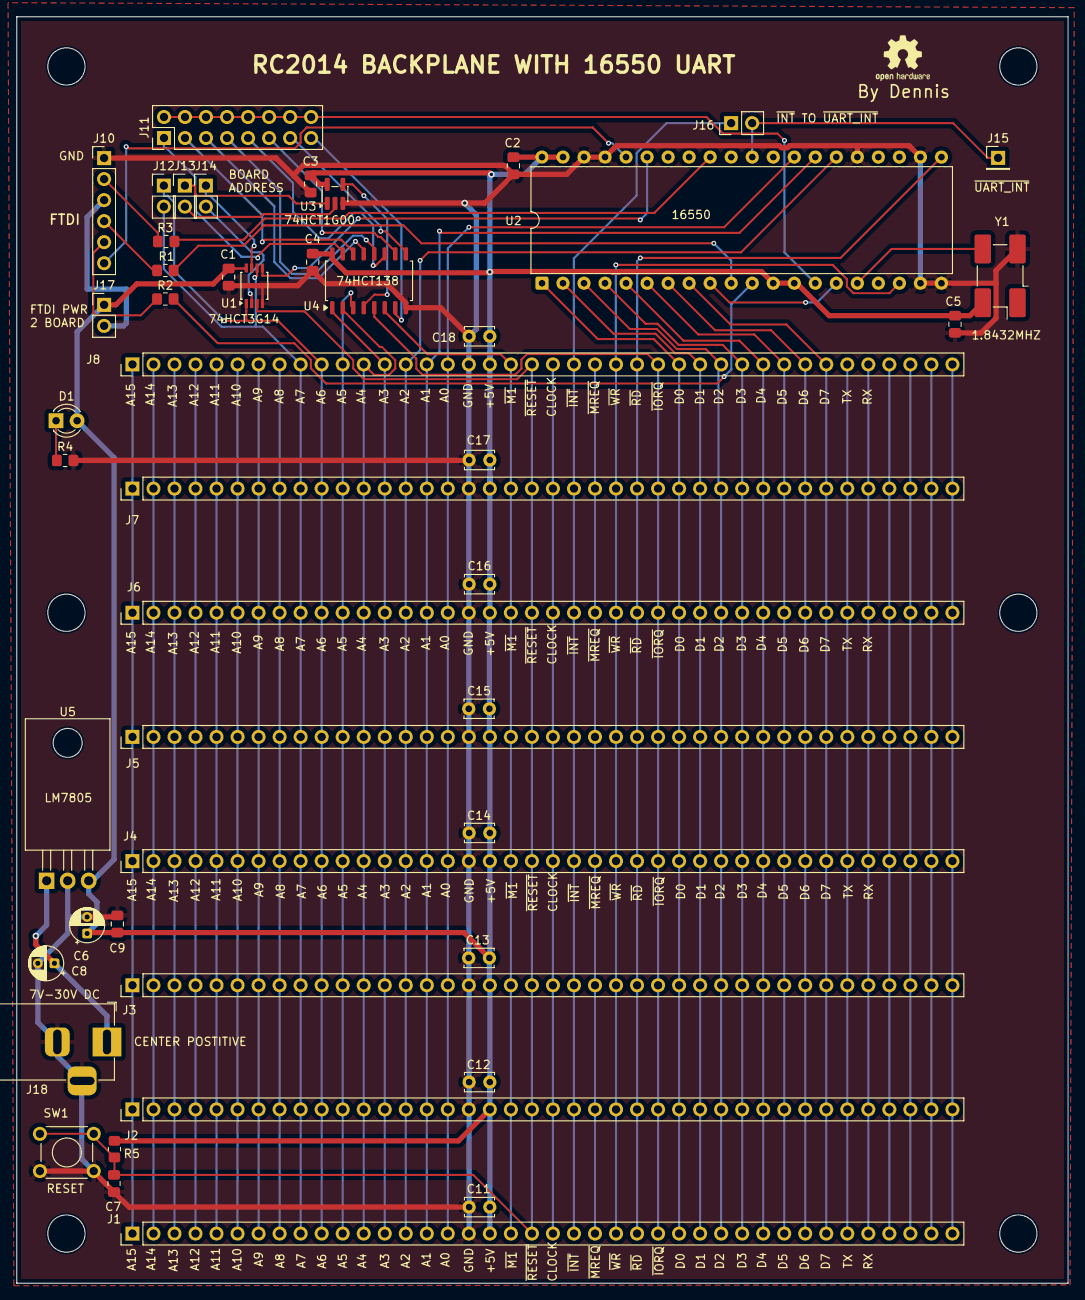
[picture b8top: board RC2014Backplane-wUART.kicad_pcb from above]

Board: 2 copper layers, 127.0 x 153.0 mm, 53 parts (0 on the bottom side), 68 nets.
